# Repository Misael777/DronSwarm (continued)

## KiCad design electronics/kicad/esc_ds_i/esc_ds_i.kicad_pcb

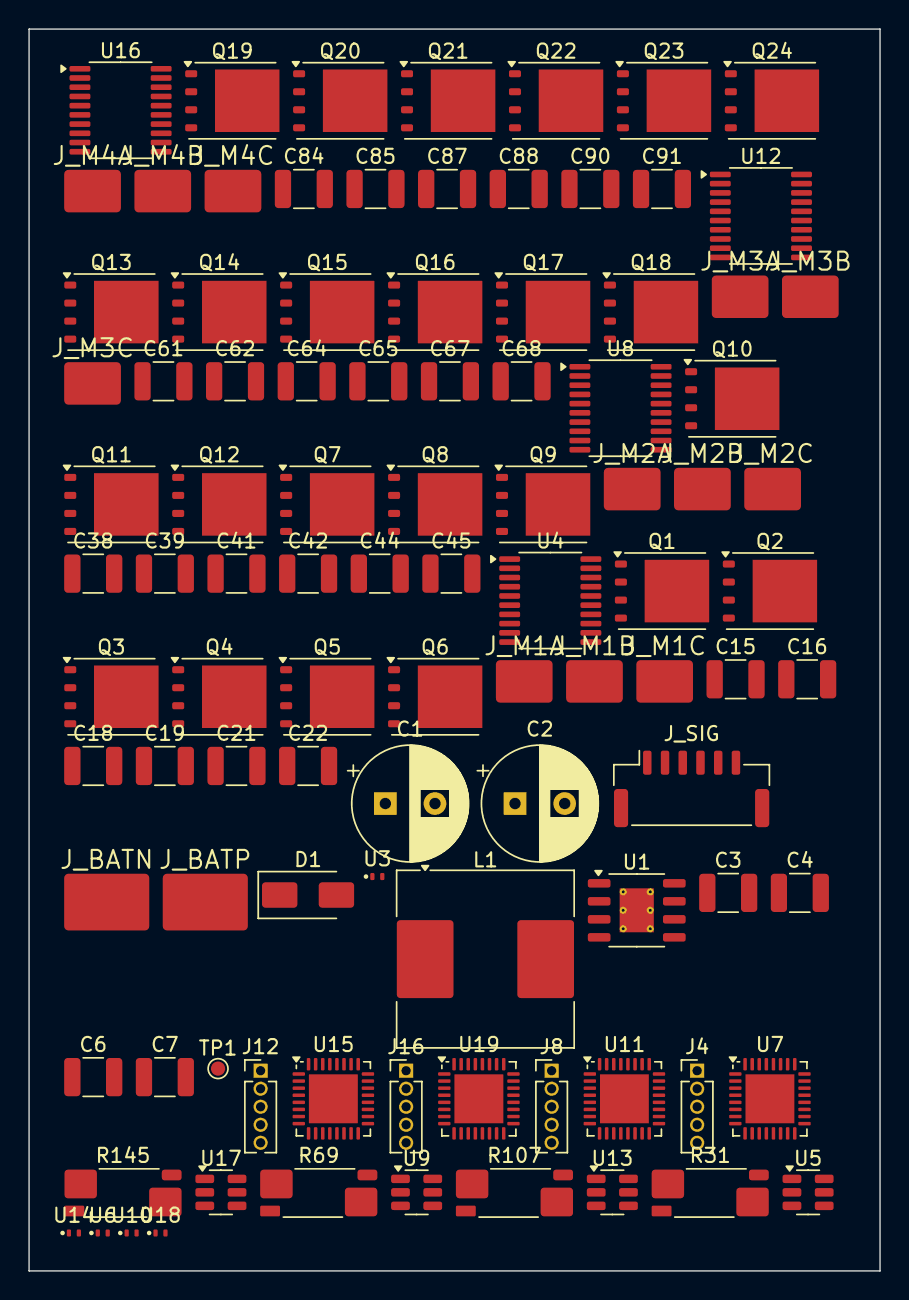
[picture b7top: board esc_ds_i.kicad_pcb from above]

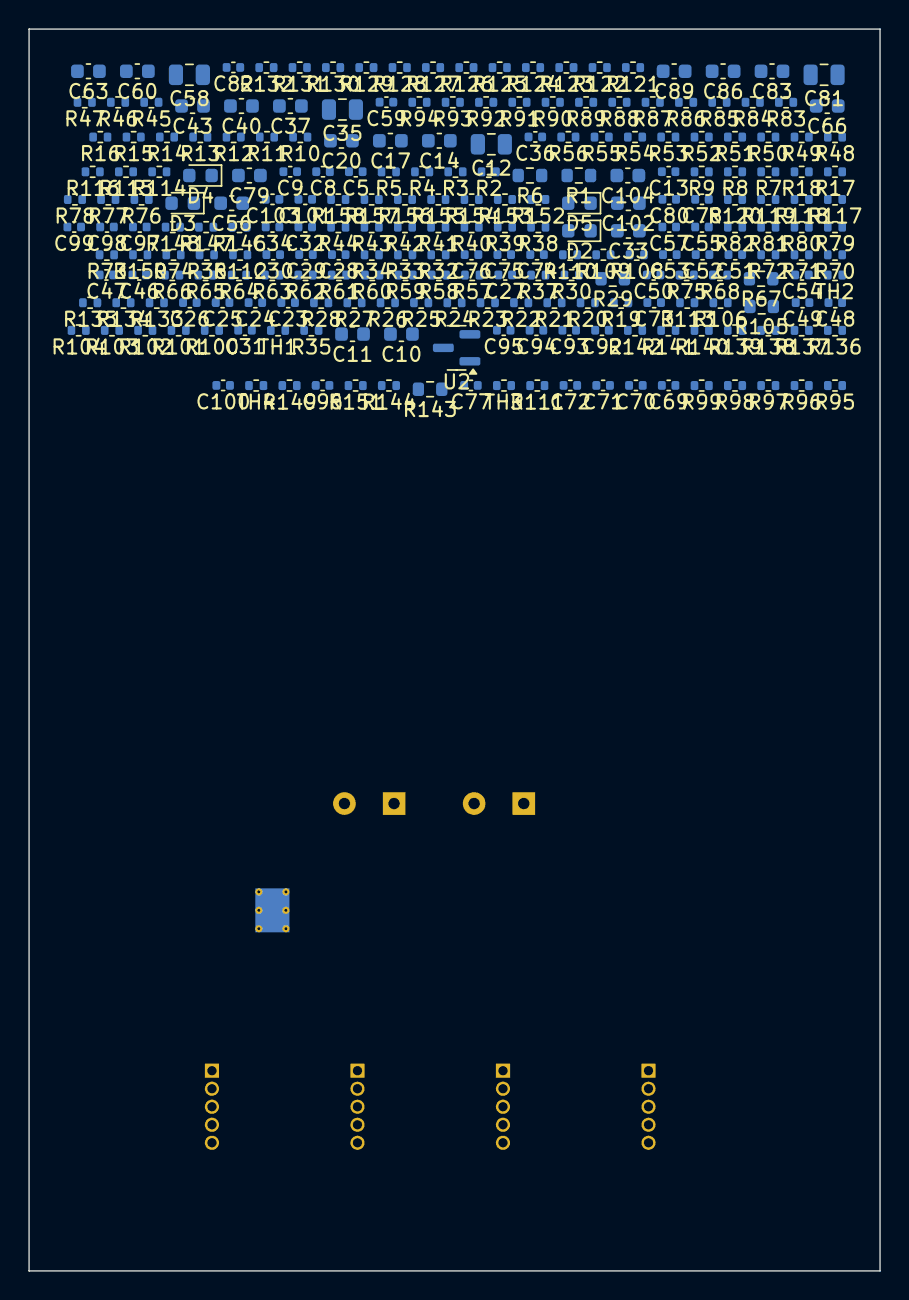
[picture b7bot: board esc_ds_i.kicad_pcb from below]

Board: 4 copper layers, 60.0 x 87.6 mm, 335 parts (237 on the bottom side), 192 nets, no tracks yet.

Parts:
C1, C2: 470u/35V; CP_Radial_D8.0mm_P3.50mm
C3, C4: 2.2u/100V; C_1210_3225Metric
C5: 2.2n/50V; C_0402_1005Metric
C6, C7: 22u/25V; C_1210_3225Metric
C8, C26, C49, C72, C95: 3.3n; C_0402_1005Metric
C9: 56p/C0G; C_0402_1005Metric
C10, C11: 1u; C_0603_1608Metric
C12, C35, C58, C81: 10u/25V; C_0805_2012Metric
C13, C27, C28, C29, C30, C31, C32, C34, C36, C50, C51, C52, C53, C54, C55, C57, C59, C73, C74, C75, C76, C77, C78, C80, C82, C96, C97, C98, C99, C100, C101, C103: 100n; C_0402_1005Metric
C14, C17, C20, C37, C40, C43, C60, C63, C66, C83, C86, C89: 100n/25V; C_0603_1608Metric
C15, C16, C18, C19, C21, C22, C38, C39, C41, C42, C44, C45, C61, C62, C64, C65, C67, C68, C84, C85, C87, C88, C90, C91: 2.2u/50V; C_1210_3225Metric
C23, C24, C25, C46, C47, C48, C69, C70, C71, C92, C93, C94: 1n; C_0402_1005Metric
C33, C56, C79, C102: 4.7u; C_0603_1608Metric
C104: 100n/50V; C_0603_1608Metric
D1: SMAJ26A; D_SMA
D2, D3, D4, D5: verde; LED_0603_1608Metric
J4, J8, J12, J16: Conn_01x05; PinHeader_1x05_P1.27mm_Vertical
J_BATN: Conn_01x01; Pad_Power_6x4mm
J_BATP: Conn_01x01; Pad_Power_6x4mm
J_M1A, J_M1B, J_M1C, J_M2A, J_M2B, J_M2C, J_M3A, J_M3B, J_M3C, J_M4A, J_M4B, J_M4C: Conn_01x01; Pad_Power_4x3mm
J_SIG: Conn_01x06; JST_GH_SM06B-GHS-TB_1x06-1MP_P1.25mm_Horizontal
L1: 68u; L_Coilcraft_MSS1246-XXX
Q1, Q2, Q3, Q4, Q5, Q6, Q7, Q8, Q9, Q10, Q11, Q12, Q13, Q14, Q15, Q16, Q17, Q18, Q19, Q20, Q21, Q22, Q23, Q24: CSD18503Q5A; TDSON-8-1
R1: 470k; R_0603_1608Metric
R2: 47k; R_0402_1005Metric
R3: 100k; R_0402_1005Metric
R4: 453k; R_0402_1005Metric
R5: 49.9k; R_0402_1005Metric
R6: 453k; R_0603_1608Metric
R7, R8, R11, R12, R15, R16, R45, R46, R49, R50, R53, R54, R83, R84, R87, R88, R91, R92, R121, R122, R125, R126, R129, R130: 4.7; R_0402_1005Metric
R9, R10, R13, R14, R17, R18, R30, R35, R38, R39, R40, R41, R42, R43, R47, R48, R51, R52, R55, R56, R68, R73, R76, R77, R78, R79, R80, R81, R85, R86, R89, R90, R93, R94, R106, R111, R114, R115, R116, R117, R118, R119, R123, R124, R127, R128, R131, R132, R144, R149, R152, R153, R154, R155, R156, R157: 10k; R_0402_1005Metric
R19, R21, R22, R24, R25, R27, R57, R59, R60, R62, R63, R65, R95, R97, R98, R100, R101, R103, R133, R135, R136, R138, R139, R141: 20k; R_0402_1005Metric
R20, R23, R26, R58, R61, R64, R96, R99, R102, R134, R137, R140: 2.2k; R_0402_1005Metric
R28, R66, R104, R142: 750; R_0402_1005Metric
R29, R67, R105, R143: 100k; R_0603_1608Metric
R31, R69, R107, R145: 1m/2W; R_Shunt_Vishay_WSK2512_6332Metric_T1.19mm
R32, R33, R70, R71, R108, R109, R146, R147: 10; R_0402_1005Metric
R34, R44, R72, R82, R110, R120, R148, R158: 1k; R_0402_1005Metric
R36, R37, R74, R75, R112, R113, R150, R151: 100; R_0402_1005Metric
TH1, TH2, TH3, TH4: 10k B3950; R_0402_1005Metric
TP1: TestPoint; TestPoint_Pad_D1.0mm
U1: LM5164DDA; HSOP-8-1EP_3.9x4.9mm_P1.27mm_EP2.41x3.1mm_ThermalVias
U2: MCP1703Ax-330xxTT; SOT-23
U3, U6, U10, U14, U18: TPD1E05U06DPY; Texas_DPY0002A_0.6x1mm_P0.65mm
U4, U8, U12, U16: DRV8300DPW; TSSOP-20_4.4x6.5mm_P0.65mm
U5, U9, U13, U17: INA181A3; SOT-23-6
U7, U11, U15, U19: STM32G071KBUxN; QFN-32-1EP_5x5mm_P0.5mm_EP3.45x3.45mm

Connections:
3V3: C11.1, C29.1, C32.1, C33.1, C52.1, C55.1, C56.1, C75.1, C78.1, C79.1, C98.1, C101.1, C102.1, J4.1, J8.1, J12.1, J16.1, R35.1, R73.1, R111.1, R149.1, U2.2, U5.6, U7.4, U9.6, U11.4, U13.6, U15.4, U17.6, U19.4
12V: C6.1, C7.1, C8.2, C10.1, C12.1, C13.1, C35.1, C36.1, C58.1, C59.1, C81.1, C82.1, L1.2, R4.1, U2.3, U4.7, U8.7, U12.7, U16.7
BEMF1_A: C23.1, R19.2, R20.1, U7.31
BEMF1_B: C24.1, R22.2, R23.1, U7.9
BEMF1_C: C25.1, R25.2, R26.1, U7.7
BEMF1_N: C26.1, R21.2, R24.2, R27.2, R28.1, U7.8, U7.10
BEMF2_A: C46.1, R57.2, R58.1, U11.31
BEMF2_B: C47.1, R60.2, R61.1, U11.9
BEMF2_C: C48.1, R63.2, R64.1, U11.7
BEMF2_N: C49.1, R59.2, R62.2, R65.2, R66.1, U11.8, U11.10
BEMF3_A: C69.1, R95.2, R96.1, U15.31
BEMF3_B: C70.1, R98.2, R99.1, U15.9
BEMF3_C: C71.1, R101.2, R102.1, U15.7
BEMF3_N: C72.1, R97.2, R100.2, R103.2, R104.1, U15.8, U15.10
BEMF4_A: C92.1, R133.2, R134.1, U19.31
BEMF4_B: C93.1, R136.2, R137.1, U19.9
BEMF4_C: C94.1, R139.2, R140.1, U19.7
BEMF4_N: C95.1, R135.2, R138.2, R141.2, R142.1, U19.8, U19.10
BUCK_EN: R1.2, R2.1, U1.3
BUCK_FB: C9.2, R4.2, R5.1, U1.5
BUCK_RA: C8.1, C9.1, R6.2
DSHOT1: R36.2, U7.13
DSHOT2: R74.2, U11.13
DSHOT3: R112.2, U15.13
DSHOT4: R150.2, U19.13
GHA1: Q1.4, R7.2, R9.1
GHA2: Q7.4, R45.2, R47.1
GHA3: Q13.4, R83.2, R85.1
GHA4: Q19.4, R121.2, R123.1
GHB1: Q3.4, R11.2, R13.1
GHB2: Q9.4, R49.2, R51.1
GHB3: Q15.4, R87.2, R89.1
GHB4: Q21.4, R125.2, R127.1
GHC1: Q5.4, R15.2, R17.1
GHC2: Q11.4, R53.2, R55.1
GHC3: Q17.4, R91.2, R93.1
GHC4: Q23.4, R129.2, R131.1
GLA1: Q2.4, R8.2, R10.1
GLA2: Q8.4, R46.2, R48.1
GLA3: Q14.4, R84.2, R86.1
GLA4: Q20.4, R122.2, R124.1
GLB1: Q4.4, R12.2, R14.1
GLB2: Q10.4, R50.2, R52.1
GLB3: Q16.4, R88.2, R90.1
GLB4: Q22.4, R126.2, R128.1
GLC1: Q6.4, R16.2, R18.1
GLC2: Q12.4, R54.2, R56.1
GLC3: Q18.4, R92.2, R94.1
GLC4: Q24.4, R130.2, R132.1
GND: C1.2, C2.2, C3.2, C4.2, C6.2, C7.2, C10.2, C11.2, C12.2, C13.2, C23.2, C24.2, C25.2, C26.2, C27.2, C29.2, C30.2, C31.2, C32.2, C33.2, C34.2, C35.2, C36.2, C46.2, C47.2, C48.2, C49.2, C50.2, C52.2, C53.2, C54.2, C55.2, C56.2, C57.2, C58.2, C59.2, C69.2, C70.2, C71.2, C72.2, C73.2, C75.2, C76.2, C77.2, C78.2, C79.2, C80.2, C81.2, C82.2, C92.2, C93.2, C94.2, C95.2, C96.2, C98.2, C99.2, C100.2, C101.2, C102.2, C103.2, C104.2, D1.2, D2.1, D3.1, D4.1, D5.1, J4.5, J8.5, J12.5, J16.5, J_BATN.1, J_SIG.1, R2.2, R3.2, R5.2, R20.2, R23.2, R26.2, R28.2, R30.2, R31.4, R38.2, R39.2, R40.2, R41.2, R42.2, R43.2, R58.2, R61.2, R64.2, R66.2, R68.2, R69.4, R76.2, R77.2, R78.2, R79.2, R80.2, R81.2, R96.2, R99.2, R102.2, R104.2, R106.2, R107.4, R114.2, R115.2, R116.2, R117.2, R118.2, R119.2, R134.2, R137.2, R140.2, R142.2, R144.2, R145.4, R152.2, R153.2, R154.2, R155.2, R156.2, R157.2, TH1.2, TH2.2, TH3.2, TH4.2, U1.1, U1.9, U2.1, U3.2, U4.8, U5.2, U5.5, U6.2, U7.5, U7.33, U8.8, U9.2, U9.5, U10.2, U11.5, U11.33, U12.8, U13.2, U13.5, U14.2, U15.5, U15.33, U16.8, U17.2, U17.5, U18.2, U19.5, U19.33
ISENSE1: C30.1, R34.2, U7.11
ISENSE2: C53.1, R72.2, U11.11
ISENSE3: C76.1, R110.2, U15.11
ISENSE4: C99.1, R148.2, U19.11
ISENSE_N: C28.2, R33.2, U5.4
ISENSE_N1: C51.2, R71.2, U9.4
ISENSE_N2: C74.2, R109.2, U13.4
ISENSE_N3: C97.2, R147.2, U17.4
ISENSE_P: C28.1, R32.2, U5.3
ISENSE_P1: C51.1, R70.2, U9.3
ISENSE_P2: C74.1, R108.2, U13.3
ISENSE_P3: C97.1, R146.2, U17.3
LED_A: D2.2, R44.2
LED_A1: D3.2, R82.2
LED_A2: D4.2, R120.2
LED_A3: D5.2, R158.2
M1_A: C14.2, J_M1A.1, Q1.1, Q1.2, Q1.3, Q2.5, R9.2, R19.1, R21.1, U4.18
M1_B: C17.2, J_M1B.1, Q3.1, Q3.2, Q3.3, Q4.5, R13.2, R22.1, R24.1, U4.15
M1_C: C20.2, J_M1C.1, Q5.1, Q5.2, Q5.3, Q6.5, R17.2, R25.1, R27.1, U4.12
M2_A: C37.2, J_M2A.1, Q7.1, Q7.2, Q7.3, Q8.5, R47.2, R57.1, R59.1, U8.18
M2_B: C40.2, J_M2B.1, Q9.1, Q9.2, Q9.3, Q10.5, R51.2, R60.1, R62.1, U8.15
M2_C: C43.2, J_M2C.1, Q11.1, Q11.2, Q11.3, Q12.5, R55.2, R63.1, R65.1, U8.12
M3_A: C60.2, J_M3A.1, Q13.1, Q13.2, Q13.3, Q14.5, R85.2, R95.1, R97.1, U12.18
M3_B: C63.2, J_M3B.1, Q15.1, Q15.2, Q15.3, Q16.5, R89.2, R98.1, R100.1, U12.15
M3_C: C66.2, J_M3C.1, Q17.1, Q17.2, Q17.3, Q18.5, R93.2, R101.1, R103.1, U12.12
M4_A: C83.2, J_M4A.1, Q19.1, Q19.2, Q19.3, Q20.5, R123.2, R133.1, R135.1, U16.18
M4_B: C86.2, J_M4B.1, Q21.1, Q21.2, Q21.3, Q22.5, R127.2, R136.1, R138.1, U16.15
M4_C: C89.2, J_M4C.1, Q23.1, Q23.2, Q23.3, Q24.5, R131.2, R139.1, R141.1, U16.12
unnamed: R3.1, U1.4
unnamed: C5.1, U1.7
unnamed: TP1.1, U1.6
unnamed: R7.1, U4.19
unnamed: R8.1, U4.11
unnamed: C14.1, U4.20
unnamed: R11.1, U4.16
unnamed: R12.1, U4.10
unnamed: C17.1, U4.17
unnamed: R15.1, U4.13
unnamed: R16.1, U4.9
unnamed: C20.1, U4.14
unnamed: R31.2, R32.1
unnamed: R31.3, R33.1
unnamed: R34.1, U5.1
unnamed: R44.1, U7.32
unnamed: J4.2, U7.24
unnamed: J4.3, U7.25
unnamed: R45.1, U8.19
unnamed: R46.1, U8.11
unnamed: C37.1, U8.20
unnamed: R49.1, U8.16
unnamed: R50.1, U8.10
unnamed: C40.1, U8.17
unnamed: R53.1, U8.13
unnamed: R54.1, U8.9
unnamed: C43.1, U8.14
unnamed: R69.2, R70.1
unnamed: R69.3, R71.1
unnamed: R72.1, U9.1
unnamed: R82.1, U11.32
unnamed: J8.2, U11.24
unnamed: J8.3, U11.25
unnamed: R83.1, U12.19
unnamed: R84.1, U12.11
unnamed: C60.1, U12.20
unnamed: R87.1, U12.16
unnamed: R88.1, U12.10
unnamed: C63.1, U12.17
unnamed: R91.1, U12.13
unnamed: R92.1, U12.9
unnamed: C66.1, U12.14
unnamed: R107.2, R108.1
unnamed: R107.3, R109.1
unnamed: R110.1, U13.1
unnamed: R120.1, U15.32
unnamed: J12.2, U15.24
unnamed: J12.3, U15.25
unnamed: R121.1, U16.19
unnamed: R122.1, U16.11
unnamed: C83.1, U16.20
unnamed: R125.1, U16.16
unnamed: R126.1, U16.10
unnamed: C86.1, U16.17
unnamed: R129.1, U16.13
unnamed: R130.1, U16.9
unnamed: C89.1, U16.14
unnamed: R145.2, R146.1
unnamed: R145.3, R147.1
unnamed: R148.1, U17.1
unnamed: R158.1, U19.32
unnamed: J16.2, U19.24
unnamed: J16.3, U19.25
NRST: C34.1, J4.4, U7.6
NRST1: C57.1, J8.4, U11.6
NRST2: C80.1, J12.4, U15.6
NRST3: C103.1, J16.4, U19.6
PGND1: C15.2, C16.2, C18.2, C19.2, C21.2, C22.2, Q2.1, Q2.2, Q2.3, Q4.1, Q4.2, Q4.3, Q6.1, Q6.2, Q6.3, R10.2, R14.2, R18.2, R31.1
PGND2: C38.2, C39.2, C41.2, C42.2, C44.2, C45.2, Q8.1, Q8.2, Q8.3, Q10.1, Q10.2, Q10.3, Q12.1, Q12.2, Q12.3, R48.2, R52.2, R56.2, R69.1
PGND3: C61.2, C62.2, C64.2, C65.2, C67.2, C68.2, Q14.1, Q14.2, Q14.3, Q16.1, Q16.2, Q16.3, Q18.1, Q18.2, Q18.3, R86.2, R90.2, R94.2, R107.1
PGND4: C84.2, C85.2, C87.2, C88.2, C90.2, C91.2, Q20.1, Q20.2, Q20.3, Q22.1, Q22.2, Q22.3, Q24.1, Q24.2, Q24.3, R124.2, R128.2, R132.2, R145.1
PWM1_A_HI: R38.1, U4.1, U7.21
PWM1_A_LO: R39.1, U4.4, U7.17
PWM1_B_HI: R40.1, U4.2, U7.19
PWM1_B_LO: R41.1, U4.5, U7.15
PWM1_C_HI: R42.1, U4.3, U7.18
PWM1_C_LO: R43.1, U4.6, U7.14
PWM2_A_HI: R76.1, U8.1, U11.21
PWM2_A_LO: R77.1, U8.4, U11.17
PWM2_B_HI: R78.1, U8.2, U11.19
PWM2_B_LO: R79.1, U8.5, U11.15
PWM2_C_HI: R80.1, U8.3, U11.18
PWM2_C_LO: R81.1, U8.6, U11.14
PWM3_A_HI: R114.1, U12.1, U15.21
PWM3_A_LO: R115.1, U12.4, U15.17
PWM3_B_HI: R116.1, U12.2, U15.19
PWM3_B_LO: R117.1, U12.5, U15.15
PWM3_C_HI: R118.1, U12.3, U15.18
PWM3_C_LO: R119.1, U12.6, U15.14
PWM4_A_HI: R152.1, U16.1, U19.21
PWM4_A_LO: R153.1, U16.4, U19.17
PWM4_B_HI: R154.1, U16.2, U19.19
PWM4_B_LO: R155.1, U16.5, U19.15
PWM4_C_HI: R156.1, U16.3, U19.18
PWM4_C_LO: R157.1, U16.6, U19.14
S1_IN: J_SIG.3, R36.1, U6.1
S2_IN: J_SIG.4, R74.1, U10.1
S3_IN: J_SIG.5, R112.1, U14.1
S4_IN: J_SIG.6, R150.1, U18.1
SW_BUCK: C5.2, L1.1, R6.1, U1.8
TEMP1: C31.1, R35.2, TH1.1, U7.16
TEMP2: C54.1, R73.2, TH2.1, U11.16
TEMP3: C77.1, R111.2, TH3.1, U15.16
TEMP4: C100.1, R149.2, TH4.1, U19.16
TLM1: R37.1, U7.30
TLM2: R75.1, U11.30
TLM3: R113.1, U15.30
TLM4: R151.1, U19.30
TLM_OUT: J_SIG.2, R37.2, R75.2, R113.2, R151.2, U3.1
VBUS: C1.1, C2.1, C3.1, C4.1, C15.1, C16.1, C18.1, C19.1, C21.1, C22.1, C38.1, C39.1, C41.1, C42.1, C44.1, C45.1, C61.1, C62.1, C64.1, C65.1, C67.1, C68.1, C84.1, C85.1, C87.1, C88.1, C90.1, C91.1, C104.1, D1.1, J_BATP.1, Q1.5, Q3.5, Q5.5, Q7.5, Q9.5, Q11.5, Q13.5, Q15.5, Q17.5, Q19.5, Q21.5, Q23.5, R1.1, R29.1, R67.1, R105.1, R143.1, U1.2
VBUS_SENSE1: C27.1, R29.2, R30.1, U7.12
VBUS_SENSE2: C50.1, R67.2, R68.1, U11.12
VBUS_SENSE3: C73.1, R105.2, R106.1, U15.12
VBUS_SENSE4: C96.1, R143.2, R144.1, U19.12

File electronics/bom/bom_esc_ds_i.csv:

Comment,Designator,Footprint,Quantity,Unit price USD (est.)
10k,"R9,R10,R13,R14,R17,R18,R30,R35,R38,R39,R40,R41,R42,R43,R47,R48,R51,R52,R55,R56,R68,R73,R76,R77,R78,R79,R80,R81,R85,R86,R89,R90,R93,R94,R106,R111,R114,R115,R116,R117,R118,R119,R123,R124,R127,R128,R131,R132,R144,R149,R152,R153,R154,R155,R156,R157",Resistor_SMD:R_0402_1005Metric,56,0.002
100n,"C13,C27,C28,C29,C30,C31,C32,C34,C36,C50,C51,C52,C53,C54,C55,C57,C59,C73,C74,C75,C76,C77,C78,C80,C82,C96,C97,C98,C99,C100,C101,C103",Capacitor_SMD:C_0402_1005Metric,32,0.004
2.2u/50V,"C15,C16,C18,C19,C21,C22,C38,C39,C41,C42,C44,C45,C61,C62,C64,C65,C67,C68,C84,C85,C87,C88,C90,C91",Capacitor_SMD:C_1210_3225Metric,24,0.1
20k,"R19,R21,R22,R24,R25,R27,R57,R59,R60,R62,R63,R65,R95,R97,R98,R100,R101,R103,R133,R135,R136,R138,R139,R141",Resistor_SMD:R_0402_1005Metric,24,0.002
4.7,"R7,R8,R11,R12,R15,R16,R45,R46,R49,R50,R53,R54,R83,R84,R87,R88,R91,R92,R121,R122,R125,R126,R129,R130",Resistor_SMD:R_0402_1005Metric,24,0.002
CSD18503Q5A,"Q1,Q2,Q3,Q4,Q5,Q6,Q7,Q8,Q9,Q10,Q11,Q12,Q13,Q14,Q15,Q16,Q17,Q18,Q19,Q20,Q21,Q22,Q23,Q24",Package_TO_SOT_SMD:TDSON-8-1,24,0.55
100n/25V,"C14,C17,C20,C37,C40,C43,C60,C63,C66,C83,C86,C89",Capacitor_SMD:C_0603_1608Metric,12,0.008
1n,"C23,C24,C25,C46,C47,C48,C69,C70,C71,C92,C93,C94",Capacitor_SMD:C_0402_1005Metric,12,0.004
2.2k,"R20,R23,R26,R58,R61,R64,R96,R99,R102,R134,R137,R140",Resistor_SMD:R_0402_1005Metric,12,0.002
Conn_01x01,"J_M1A,J_M2A,J_M3A,J_M4A,J_M1B,J_M2B,J_M3B,J_M4B,J_M1C,J_M2C,J_M3C,J_M4C",DronSwarm:Pad_Power_4x3mm,12,0.0
10,"R32,R33,R70,R71,R108,R109,R146,R147",Resistor_SMD:R_0402_1005Metric,8,0.002
100,"R36,R37,R74,R75,R112,R113,R150,R151",Resistor_SMD:R_0402_1005Metric,8,0.002
1k,"R34,R44,R72,R82,R110,R120,R148,R158",Resistor_SMD:R_0402_1005Metric,8,0.002
3.3n,"C8,C26,C49,C72,C95",Capacitor_SMD:C_0402_1005Metric,5,0.004
TPD1E05U06DPY,"U3,U6,U10,U14,U18",Package_SON:Texas_DPY0002A_0.6x1mm_P0.65mm,5,0.08
100k,"R29,R67,R105,R143",Resistor_SMD:R_0603_1608Metric,4,0.003
10k B3950,"TH1,TH2,TH3,TH4",Resistor_SMD:R_0402_1005Metric,4,0.03
10u/25V,"C12,C35,C58,C81",Capacitor_SMD:C_0805_2012Metric,4,0.03
1m/2W,"R31,R69,R107,R145",Resistor_SMD:R_Shunt_Vishay_WSK2512_6332Metric_T1.19mm,4,0.35
4.7u,"C33,C56,C79,C102",Capacitor_SMD:C_0603_1608Metric,4,0.008
750,"R28,R66,R104,R142",Resistor_SMD:R_0402_1005Metric,4,0.002
Conn_01x05,"J4,J8,J12,J16",Connector_PinHeader_1.27mm:PinHeader_1x05_P1.27mm_Vertical,4,0.05
DRV8300DPW,"U4,U8,U12,U16",Package_SO:TSSOP-20_4.4x6.5mm_P0.65mm,4,0.85
INA181A3,"U5,U9,U13,U17",Package_TO_SOT_SMD:SOT-23-6,4,0.35
STM32G071KBUxN,"U7,U11,U15,U19",Package_DFN_QFN:QFN-32-1EP_5x5mm_P0.5mm_EP3.45x3.45mm,4,1.6
verde,"D2,D3,D4,D5",LED_SMD:LED_0603_1608Metric,4,0.02
1u,"C10,C11",Capacitor_SMD:C_0603_1608Metric,2,0.008
2.2u/100V,"C3,C4",Capacitor_SMD:C_1210_3225Metric,2,0.15
22u/25V,"C6,C7",Capacitor_SMD:C_1210_3225Metric,2,0.12
470u/35V,"C1,C2",Capacitor_THT:CP_Radial_D8.0mm_P3.50mm,2,0.25
Conn_01x01,"J_BATN,J_BATP",DronSwarm:Pad_Power_6x4mm,2,0.0
100k,R3,Resistor_SMD:R_0402_1005Metric,1,0.002
100n/50V,C104,Capacitor_SMD:C_0603_1608Metric,1,0.008
2.2n/50V,C5,Capacitor_SMD:C_0402_1005Metric,1,0.004
453k,R4,Resistor_SMD:R_0402_1005Metric,1,0.002
453k,R6,Resistor_SMD:R_0603_1608Metric,1,0.003
470k,R1,Resistor_SMD:R_0603_1608Metric,1,0.003
47k,R2,Resistor_SMD:R_0402_1005Metric,1,0.002
49.9k,R5,Resistor_SMD:R_0402_1005Metric,1,0.002
56p/C0G,C9,Capacitor_SMD:C_0402_1005Metric,1,0.004
68u,L1,Inductor_SMD:L_Coilcraft_MSS1246-XXX,1,0.45
Conn_01x06,J_SIG,Connector_JST:JST_GH_SM06B-GHS-TB_1x06-1MP_P1.25mm_Horizontal,1,0.24
LM5164DDA,U1,Package_SO:HSOP-8-1EP_3.9x4.9mm_P1.27mm_EP2.41x3.1mm_ThermalVias,1,1.4
MCP1703Ax-330xxTT,U2,Package_TO_SOT_SMD:SOT-23,1,0.35
SMAJ26A,D1,Diode_SMD:D_SMA,1,0.08
TestPoint,TP1,TestPoint:TestPoint_Pad_D1.0mm,1,0.0
